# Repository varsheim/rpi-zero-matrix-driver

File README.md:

# rpi-zero-matrix-driver
Raspberry PI breakout board to run my tesseract matrix

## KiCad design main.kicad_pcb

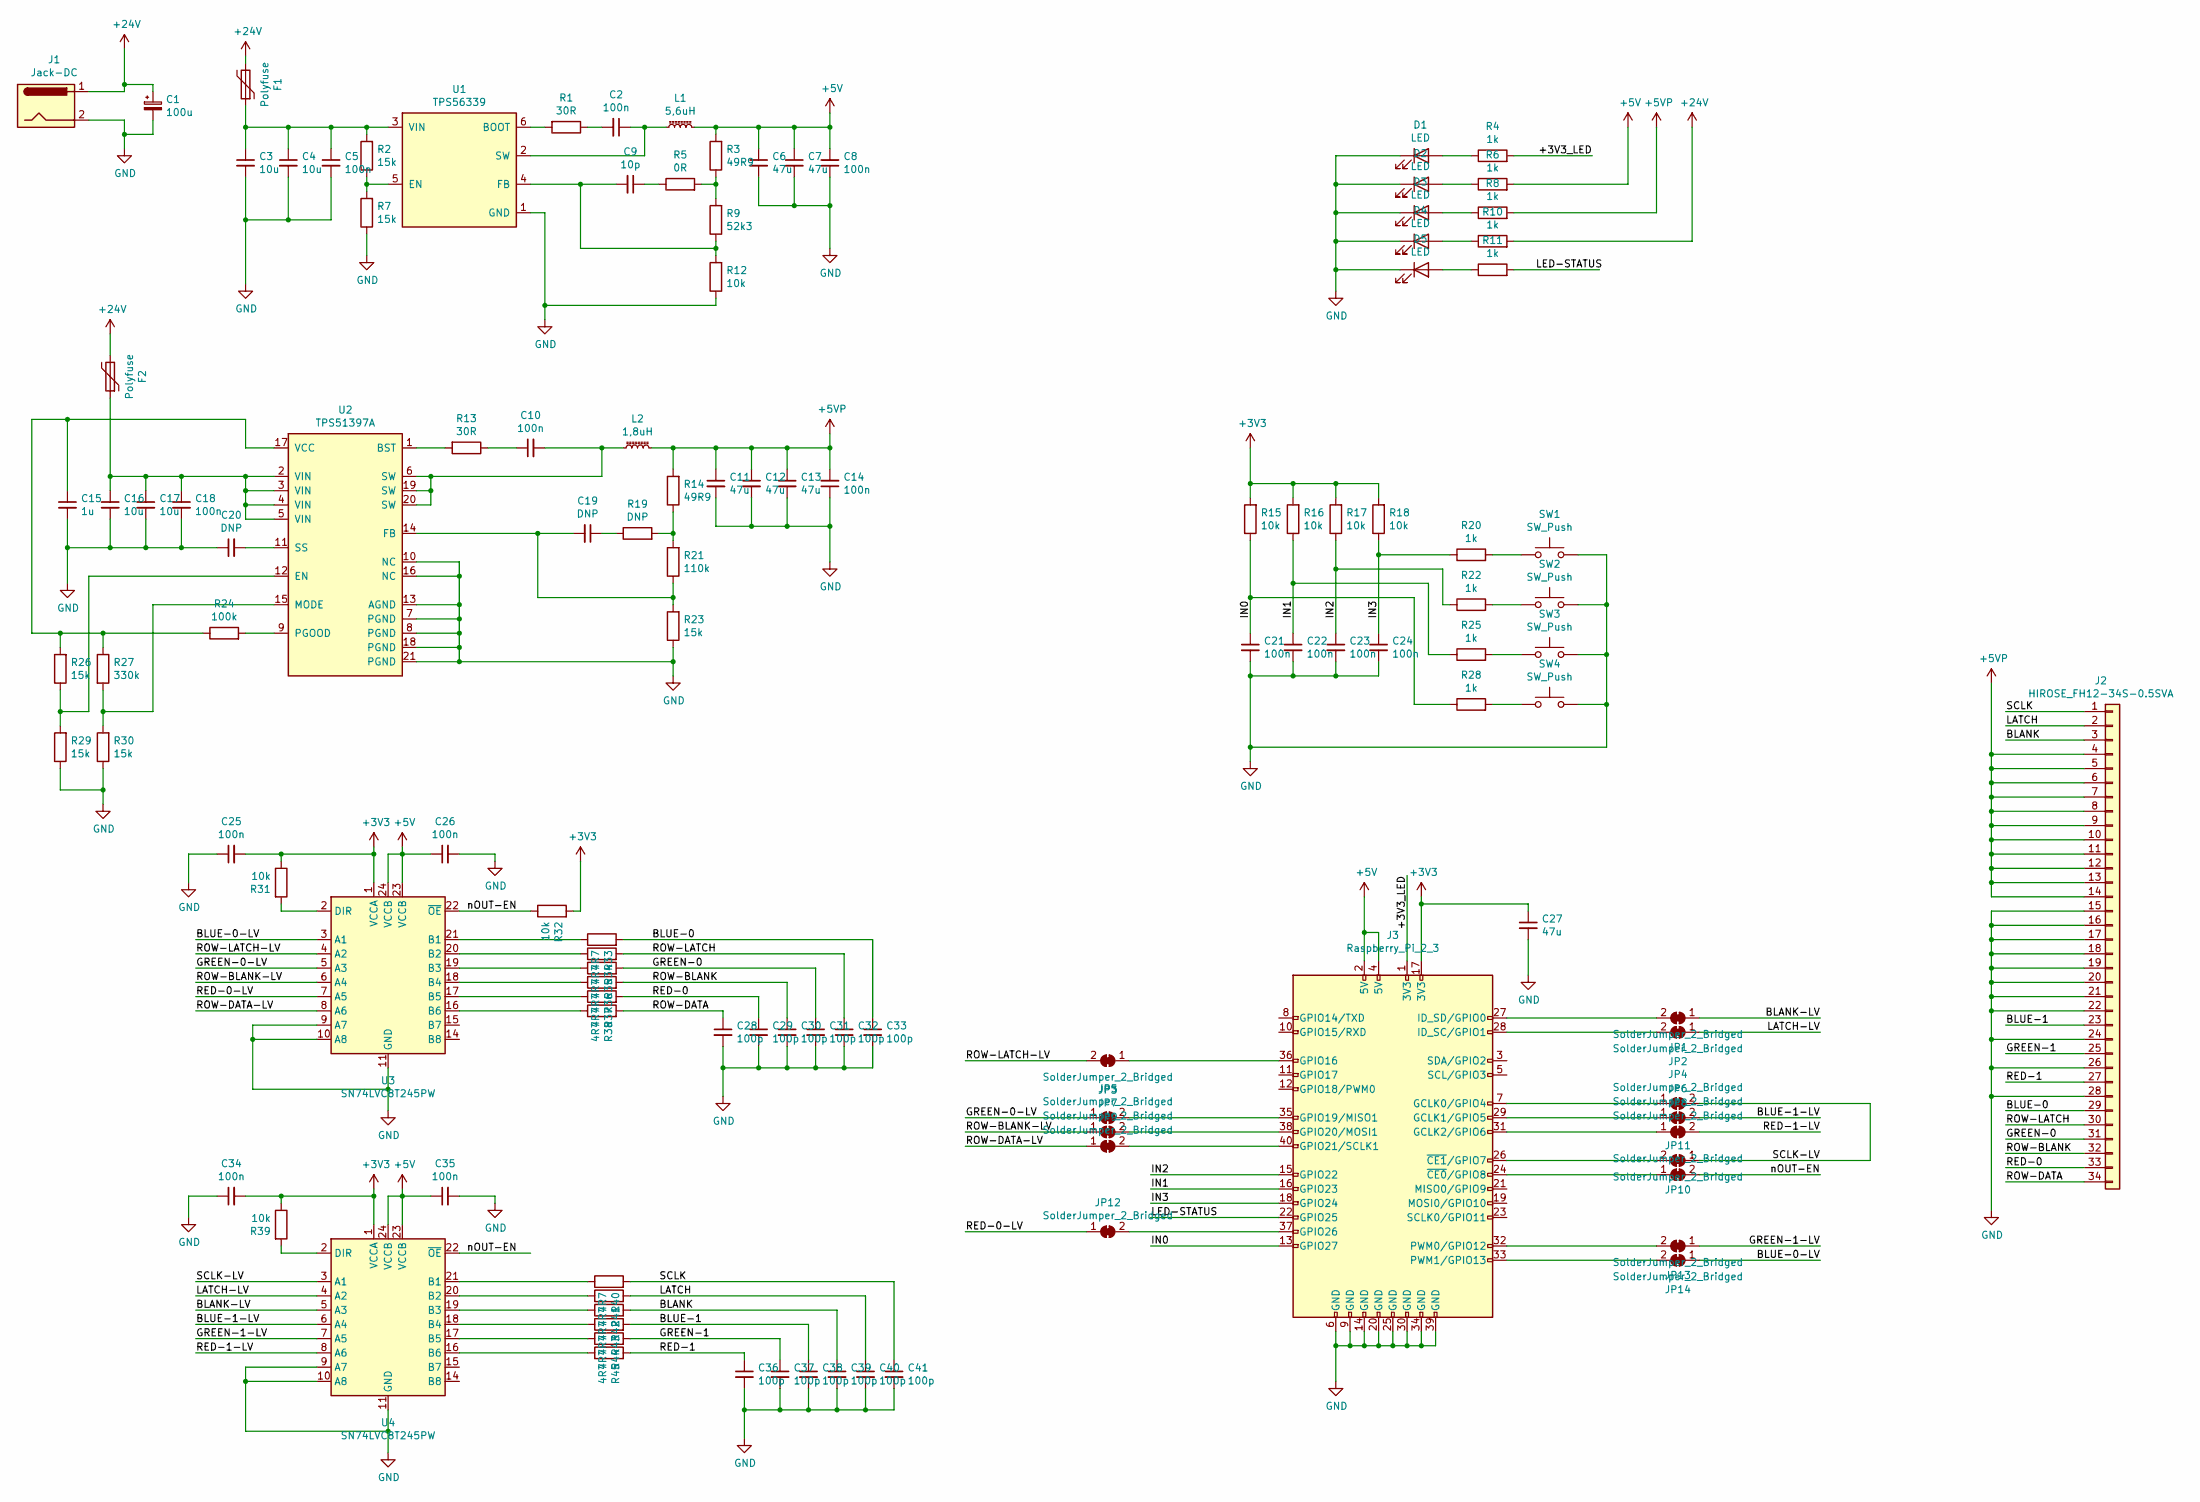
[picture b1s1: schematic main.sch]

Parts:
C1: 100u; CP_Elec_8x10.5
C2, C5, C8, C10, C14, C18, C21, C22, C23, C24, C25, C26, C34, C35: 100n; C_0603_1608Metric
C3, C4, C16, C17: 10u; C_1210_3225Metric
C6, C7, C11, C12, C13, C27: 47u; C_1206_3216Metric
C9: 10p; C_0603_1608Metric
C15: 1u; C_1206_3216Metric
C19, C20: DNP; C_0603_1608Metric
C28, C29, C30, C31, C32, C33, C36, C37, C38, C39, C40, C41: 100p; C_0603_1608Metric
D1, D2, D3, D4, D5: LED; LED_0603_1608Metric
F1, F2: Polyfuse; Fuse_0805_2012Metric
J1: Jack-DC; BarrelJack_CUI_PJ-063AH_Horizontal
J2: HIROSE_FH12-34S-0.5SVA
J3: Raspberry_Pi_2_3; Raspberry_Pi_Zero_Socketed_THT_FaceDown_MountingHoles
JP1, JP2, JP3, JP4, JP5, JP6, JP7, JP8, JP9, JP10, JP11, JP12, JP13, JP14: SolderJumper_2_Bridged; SolderJumper-2_P1.3mm_Open_RoundedPad1.0x1.5mm
L1: 5,6uH; L_Wuerth_MAPI-4020
L2: 1,8uH; L_Wuerth_HCI-1050
R1, R13: 30R; R_0603_1608Metric
R2, R7, R23, R26, R29, R30: 15k; R_0603_1608Metric
R3, R14: 49R9; R_0603_1608Metric
R4, R6, R8, R10, R11, R20, R22, R25, R28: 1k; R_0603_1608Metric
R5: 0R; R_0603_1608Metric
R9: 52k3; R_0603_1608Metric
R12, R15, R16, R17, R18, R31, R32, R39: 10k; R_0603_1608Metric
R19: DNP; R_0603_1608Metric
R21: 110k; R_0603_1608Metric
R24: 100k; R_0603_1608Metric
R27: 330k; R_0603_1608Metric
R33, R34, R35, R36, R37, R38, R40, R41, R42, R43, R44, R45: 4R7; R_0603_1608Metric
SW1, SW2, SW3, SW4: SW_Push; SW_SPST_TL3305A
U1: TPS56339; SOT-23-6
U2: TPS51397A; VQFN-20-1EP_3x3mm_P0.45mm_EP1.55x1.55mm
U3, U4: SN74LVC8T245PW; TSSOP-24_4.4x7.8mm_P0.65mm

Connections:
+3V3: C25.2, C27.1, C34.2, J3.17 (3V3), R15.2, R16.2, R17.2, R18.2, R31.1, R32.2, R39.1, U3.1 (VCCA), U4.1 (VCCA)
+5V: C6.1, C7.1, C8.2, C26.1, C35.1, J3.2 (5V), J3.4 (5V), L1.2, R3.2, R6.2, U3.23 (VCCB), U3.24 (VCCB), U4.23 (VCCB), U4.24 (VCCB)
+5VP: C11.1, C12.1, C13.1, C14.2, J2.4, J2.5, J2.6, J2.7, J2.8, J2.9, J2.10, J2.11, J2.12, J2.13, J2.14, L2.2, R8.2, R14.2
+24V: C1.1, F1.2, F2.2, J1.1, R10.2
/+3V3_LED: J3.1 (3V3), R4.2
/BLANK: C39.1, J2.3, R42.2
/BLANK-LV: JP1.1 (A), U4.5 (A3)
/BLUE-0: C33.1, J2.29, R33.2
/BLUE-0-LV: JP14.1 (A), U3.3 (A1)
/BLUE-1: C38.1, J2.23, R43.2
/BLUE-1-LV: JP6.2 (B), U4.6 (A4)
/GREEN-0: C31.1, J2.31, R35.2
/GREEN-0-LV: JP5.1 (A), U3.5 (A3)
/GREEN-1: C37.1, J2.25, R44.2
/GREEN-1-LV: JP13.1 (A), U4.7 (A5)
/IN0: C21.1, J3.13 (GPIO27), R15.1, R28.1
/IN1: C22.1, J3.16 (GPIO23), R16.1, R25.1
/IN2: C23.1, J3.15 (GPIO22), R17.1, R22.1
/IN3: C24.1, J3.18 (GPIO24), R18.1, R20.1
/LATCH: C40.1, J2.2, R41.2
/LATCH-LV: JP2.1 (A), U4.4 (A2)
/LED-STATUS: J3.22 (GPIO25), R11.2
/RED-0: C29.1, J2.33, R37.2
/RED-0-LV: JP12.1 (A), U3.7 (A5)
/RED-1: C36.1, J2.27, R45.2
/RED-1-LV: JP8.2 (B), U4.8 (A6)
/ROW-BLANK: C30.1, J2.32, R36.2
/ROW-BLANK-LV: JP7.1 (A), U3.6 (A4)
/ROW-DATA: C28.1, J2.34, R38.2
/ROW-DATA-LV: JP9.1 (A), U3.8 (A6)
/ROW-LATCH: C32.1, J2.30, R34.2
/ROW-LATCH-LV: JP3.2 (B), U3.4 (A2)
/SCLK: C41.1, J2.1, R40.2
/SCLK-LV: JP4.2 (B), JP10.1 (A), U4.3 (A1)
/nOUT-EN: JP11.2 (B), R32.1, U3.22 (~OE), U4.22 (~OE)
GND: C1.2, C3.2, C4.2, C5.2, C6.2, C7.2, C8.1, C11.2, C12.2, C13.2, C14.1, C15.2, C16.2, C17.2, C18.2, C20.1, C21.2, C22.2, C23.2, C24.2, C25.1, C26.2, C27.2, C28.2, C29.2, C30.2, C31.2, C32.2, C33.2, C34.1, C35.2, C36.2, C37.2, C38.2, C39.2, C40.2, C41.2, D1.1 (K), D2.1 (K), D3.1 (K), D4.1 (K), D5.1 (K), J1.2, J2.15, J2.16, J2.17, J2.18, J2.19, J2.20, J2.21, J2.22, J2.24, J2.26, J2.28, J3.6 (GND), J3.9 (GND), J3.14 (GND), J3.20 (GND), J3.25 (GND), J3.30 (GND), J3.34 (GND), J3.39 (GND), R7.1, R12.1, R23.1, R29.1, R30.1, SW1.2, SW2.2, SW3.2, SW4.2, U1.1 (GND), U2.7 (PGND), U2.8 (PGND), U2.10 (NC), U2.13 (AGND), U2.16 (NC), U2.18 (PGND), U2.21 (PGND), U3.9 (A7), U3.10 (A8), U3.11 (GND), U3.12 (GND), U3.13 (GND), U4.9 (A7), U4.10 (A8), U4.11 (GND), U4.12 (GND), U4.13 (GND)
unnamed: C2.1, L1.1, U1.2 (SW)
unnamed: C2.2, R1.1
unnamed: C3.1, C4.1, C5.1, F1.1, R2.2, U1.3 (VIN)
unnamed: C9.1, R5.1
unnamed: C9.2, R9.1, R12.2, U1.4 (FB)
unnamed: C10.1, R13.1
unnamed: C10.2, L2.1, U2.6 (SW), U2.19 (SW), U2.20 (SW)
unnamed: C15.1, R24.1, R26.2, R27.1, U2.17 (VCC)
unnamed: C16.1, C17.1, C18.1, F2.1, U2.2 (VIN), U2.3 (VIN), U2.4 (VIN), U2.5 (VIN)
unnamed: C19.1, R19.1
unnamed: C19.2, R21.1, R23.2, U2.14 (FB)
unnamed: C20.2, U2.11 (SS)
unnamed: D1.2 (A), R4.1
unnamed: D2.2 (A), R6.1
unnamed: D3.2 (A), R8.1
unnamed: D4.2 (A), R10.1
unnamed: D5.2 (A), R11.1
unnamed: J3.7 (GCLK0/GPIO4), JP4.1 (A)
unnamed: J3.24 (~CE0~/GPIO8), JP11.1 (A)
unnamed: J3.26 (~CE1~/GPIO7), JP10.2 (B)
unnamed: J3.27 (ID_SD/GPIO0), JP1.2 (B)
unnamed: J3.28 (ID_SC/GPIO1), JP2.2 (B)
unnamed: J3.29 (GCLK1/GPIO5), JP6.1 (A)
unnamed: J3.31 (GCLK2/GPIO6), JP8.1 (A)
unnamed: J3.32 (PWM0/GPIO12), JP13.2 (B)
unnamed: J3.33 (PWM1/GPIO13), JP14.2 (B)
unnamed: J3.35 (GPIO19/MISO1), JP5.2 (B)
unnamed: J3.36 (GPIO16), JP3.1 (A)
unnamed: J3.37 (GPIO26), JP12.2 (B)
unnamed: J3.38 (GPIO20/MOSI1), JP7.2 (B)
unnamed: J3.40 (GPIO21/SCLK1), JP9.2 (B)
unnamed: R1.2, U1.6 (BOOT)
unnamed: R2.1, R7.2, U1.5 (EN)
unnamed: R3.1, R5.2, R9.2
unnamed: R13.2, U2.1 (BST)
unnamed: R14.1, R19.2, R21.2
unnamed: R20.2, SW1.1
unnamed: R22.2, SW2.1
unnamed: R24.2, U2.9 (PGOOD)
unnamed: R25.2, SW3.1
unnamed: R26.1, R29.2, U2.12 (EN)
unnamed: R27.2, R30.2, U2.15 (MODE)
unnamed: R28.2, SW4.1
unnamed: R31.2, U3.2 (DIR)
unnamed: R33.1, U3.21 (B1)
unnamed: R34.1, U3.20 (B2)
unnamed: R35.1, U3.19 (B3)
unnamed: R36.1, U3.18 (B4)
unnamed: R37.1, U3.17 (B5)
unnamed: R38.1, U3.16 (B6)
unnamed: R39.2, U4.2 (DIR)
unnamed: R40.1, U4.21 (B1)
unnamed: R41.1, U4.20 (B2)
unnamed: R42.1, U4.19 (B3)
unnamed: R43.1, U4.18 (B4)
unnamed: R44.1, U4.17 (B5)
unnamed: R45.1, U4.16 (B6)

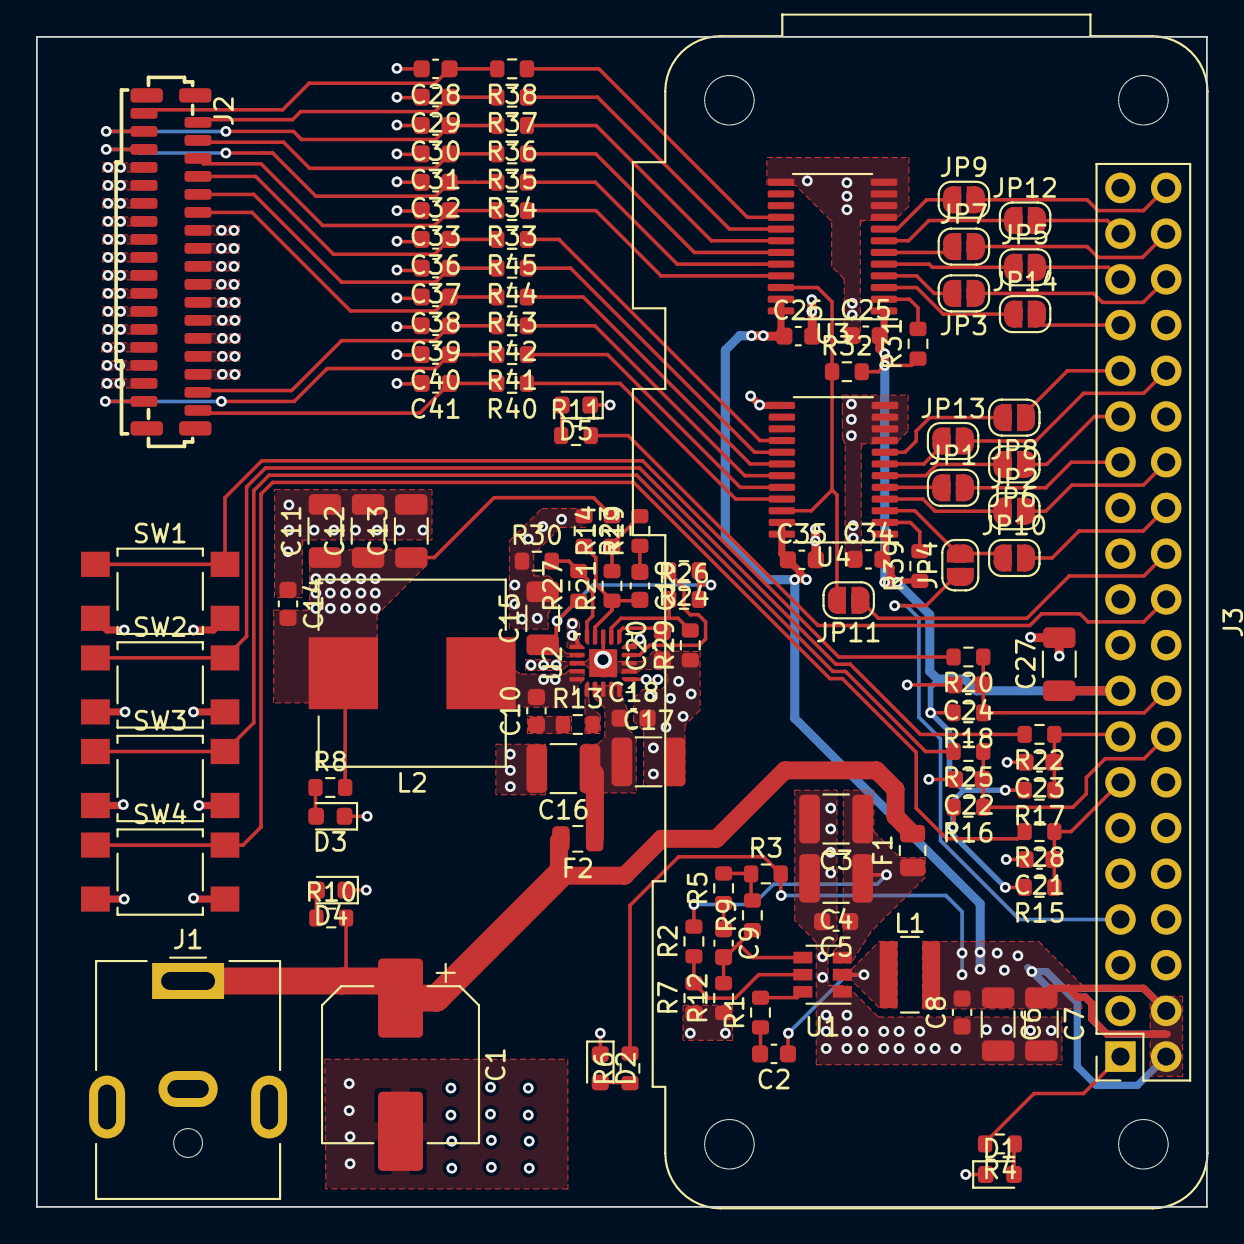
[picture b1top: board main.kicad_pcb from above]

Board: 2 copper layers, 65.0 x 65.0 mm, 120 parts (0 on the bottom side), 93 nets.

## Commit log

2021-05-01 placed all components
2021-05-02 almost routed
2021-05-03 routed
